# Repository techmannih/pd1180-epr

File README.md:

# NEMA34 48 V EPR controller — RP2040 redesign

[System block diagrams and operating sequence](https://github.com/techmannih/pd1180-epr/blob/main/docs/system-overview.md).

**Design revision 0.5.0-RP2040-DRAFT — implementation and commissioning handoff.** The source now uses RP2040, DRV8262DDVR with integrated power bridges, TPS26750 for the retained 48 V / 5 A EPR input, and an optional AS5600. The stocked-driver ECO follows merged PR #27 (`5035034`) and retains that 48 V architecture. Use the assembly and commissioning guides below to prepare the order and collect physical results after assembly.

Start with [the nine-sheet power/component review](https://github.com/techmannih/pd1180-epr/blob/main/docs/usb-pd-architecture.md), [current reference-board decisions](https://github.com/techmannih/pd1180-epr/blob/main/docs/reference-review.md), [the redesign and evidence](https://github.com/techmannih/pd1180-epr/blob/main/docs/rp2040-redesign.md), [reviewer checklist](https://github.com/techmannih/pd1180-epr/blob/main/docs/reviewer-checklist.md) and [firmware instructions](https://github.com/techmannih/pd1180-epr/blob/main/firmware/README.md). `index.circuit.tsx` is the current schematic/placement source. The DATA-only source, firmware and native route are synchronized. The paired native review archive contains fresh DRC/ERC reports: 8 retained USB hole-clearance errors, 488 cosmetic warnings, and zero other errors, unconnected items or schematic-parity/ERC findings. The older GUI screenshot is explicitly historical.

The new commissioning firmware is an ARM RP2040 image with verified ELF/BIN/UF2 format and matching source hashes. The default image remains diagnostics-only. Separate stationary-power and bounded motor-test profiles provide the post-assembly workflow: <=0.8 A RMS request, 10 rpm, 10 seconds, local START and automatic stop. Use [programming, readback and commissioning](https://github.com/techmannih/pd1180-epr/blob/main/docs/commissioning.md). Physical measurements are performed by the assembly/test team; the software results do not claim them.

The hosted preview opens `release/circuit.json`; its routed payload has been regenerated from the verified native board and checked against this DATA-only source. `index.circuit.tsx` remains editable; `bun run dev` opens that source. The PCB carries the matching 0.5 DRAFT revision marking.

| Function | This design |
| --- | --- |
| U16 MCU / U17 boot storage | RP2040 / W25Q32JV, 4 MiB QSPI flash, 12 MHz crystal; powered only from J10 DATA |
| U7 motor stage | DRV8262DDVR, top-cooled DDV package; PH/EN motion with U42 MCP4822 dual current references |
| Power | TPS26750 EPR sink, dedicated J1; independent DATA/logic-power J10 |
| PD monitoring | U38 INA237 measures raw PD_VBUS; ADS1115 retains protected VMOTOR. Fresh ADC conversion + TPS contract produce PD_READY; eFuse MOTOR_PG stays independent. |
| Terminals | J2 WAGO 2601-3104 motor; J3 WAGO 236-402 brake. No JST mating plugs; paired solder tails belong to each wire entry. |
| Encoder | AS5600 I²C, optional DNP U18 on bottom; C52/C53 on top |
| Protection | Independent eFuse, voltage window, thermal inhibit, hardware enable gates and external J3 braking resistor retained |
| Motor | STEPPERONLINE 34HS31-6004S1, 6 A/phase motor rating; initial bench-test requests <=0.8 A RMS |
| Mounting | Four motor-CAD-aligned holes; choose screws/spacers from measured rear thread/depth and physical fit |

For order preparation, use [fabrication and assembly instructions](https://github.com/techmannih/pd1180-epr/blob/main/docs/assembly.md), [the exact-part sourcing snapshot](https://github.com/techmannih/pd1180-epr/blob/main/docs/procurement.md) and [manufacturer acceptance checklist](https://github.com/techmannih/pd1180-epr/blob/main/docs/manufacturing-acceptance.md). They separate the supplied files/software from supplier allocation, installation and post-assembly measurements.

Source/firmware development checks:

```sh
bun install --frozen-lockfile
bunx tsci build index.circuit.tsx --routing-disabled --disable-parts-engine
bun run typecheck
bun run check:firmware-pins
bun run check:firmware
bun test scripts/rp2040-contract.test.mjs scripts/encoder-bypass-policy.test.mjs
bun run check:schematic-style
```

Run `bun run review` for all engineering and artifact checks; consult its generated report. The machine-readable release record separately retains manufacturer acceptance, sourcing and physical-test evidence.

The completed reviewer scope and remaining physical acceptance steps are in [the handoff](https://github.com/techmannih/pd1180-epr/blob/main/docs/completion-handoff.md). The [ordered-motor manufacturer STEP archive](https://github.com/techmannih/pd1180-epr/blob/main/engineering/mechanical/34HS31-6004S1-manufacturer.zip) establishes the rear hole axes; it does not approve replacement screws or engagement depth.

Previous-board context: [historical README](https://github.com/techmannih/pd1180-epr/blob/main/docs/legacy-stm32-tmc-readme.md). It is retained for review, not as evidence for the redesign.

**DATA-only MCU:** J10 supplies RP2040 even when J1 PD is connected. PD alone cannot run local controls. Board-side I²C and status signals are isolated through U39/U40; the brake retains independent motor-bus power. See [power domains](https://github.com/techmannih/pd1180-epr/blob/main/docs/usb-pd-architecture.md).

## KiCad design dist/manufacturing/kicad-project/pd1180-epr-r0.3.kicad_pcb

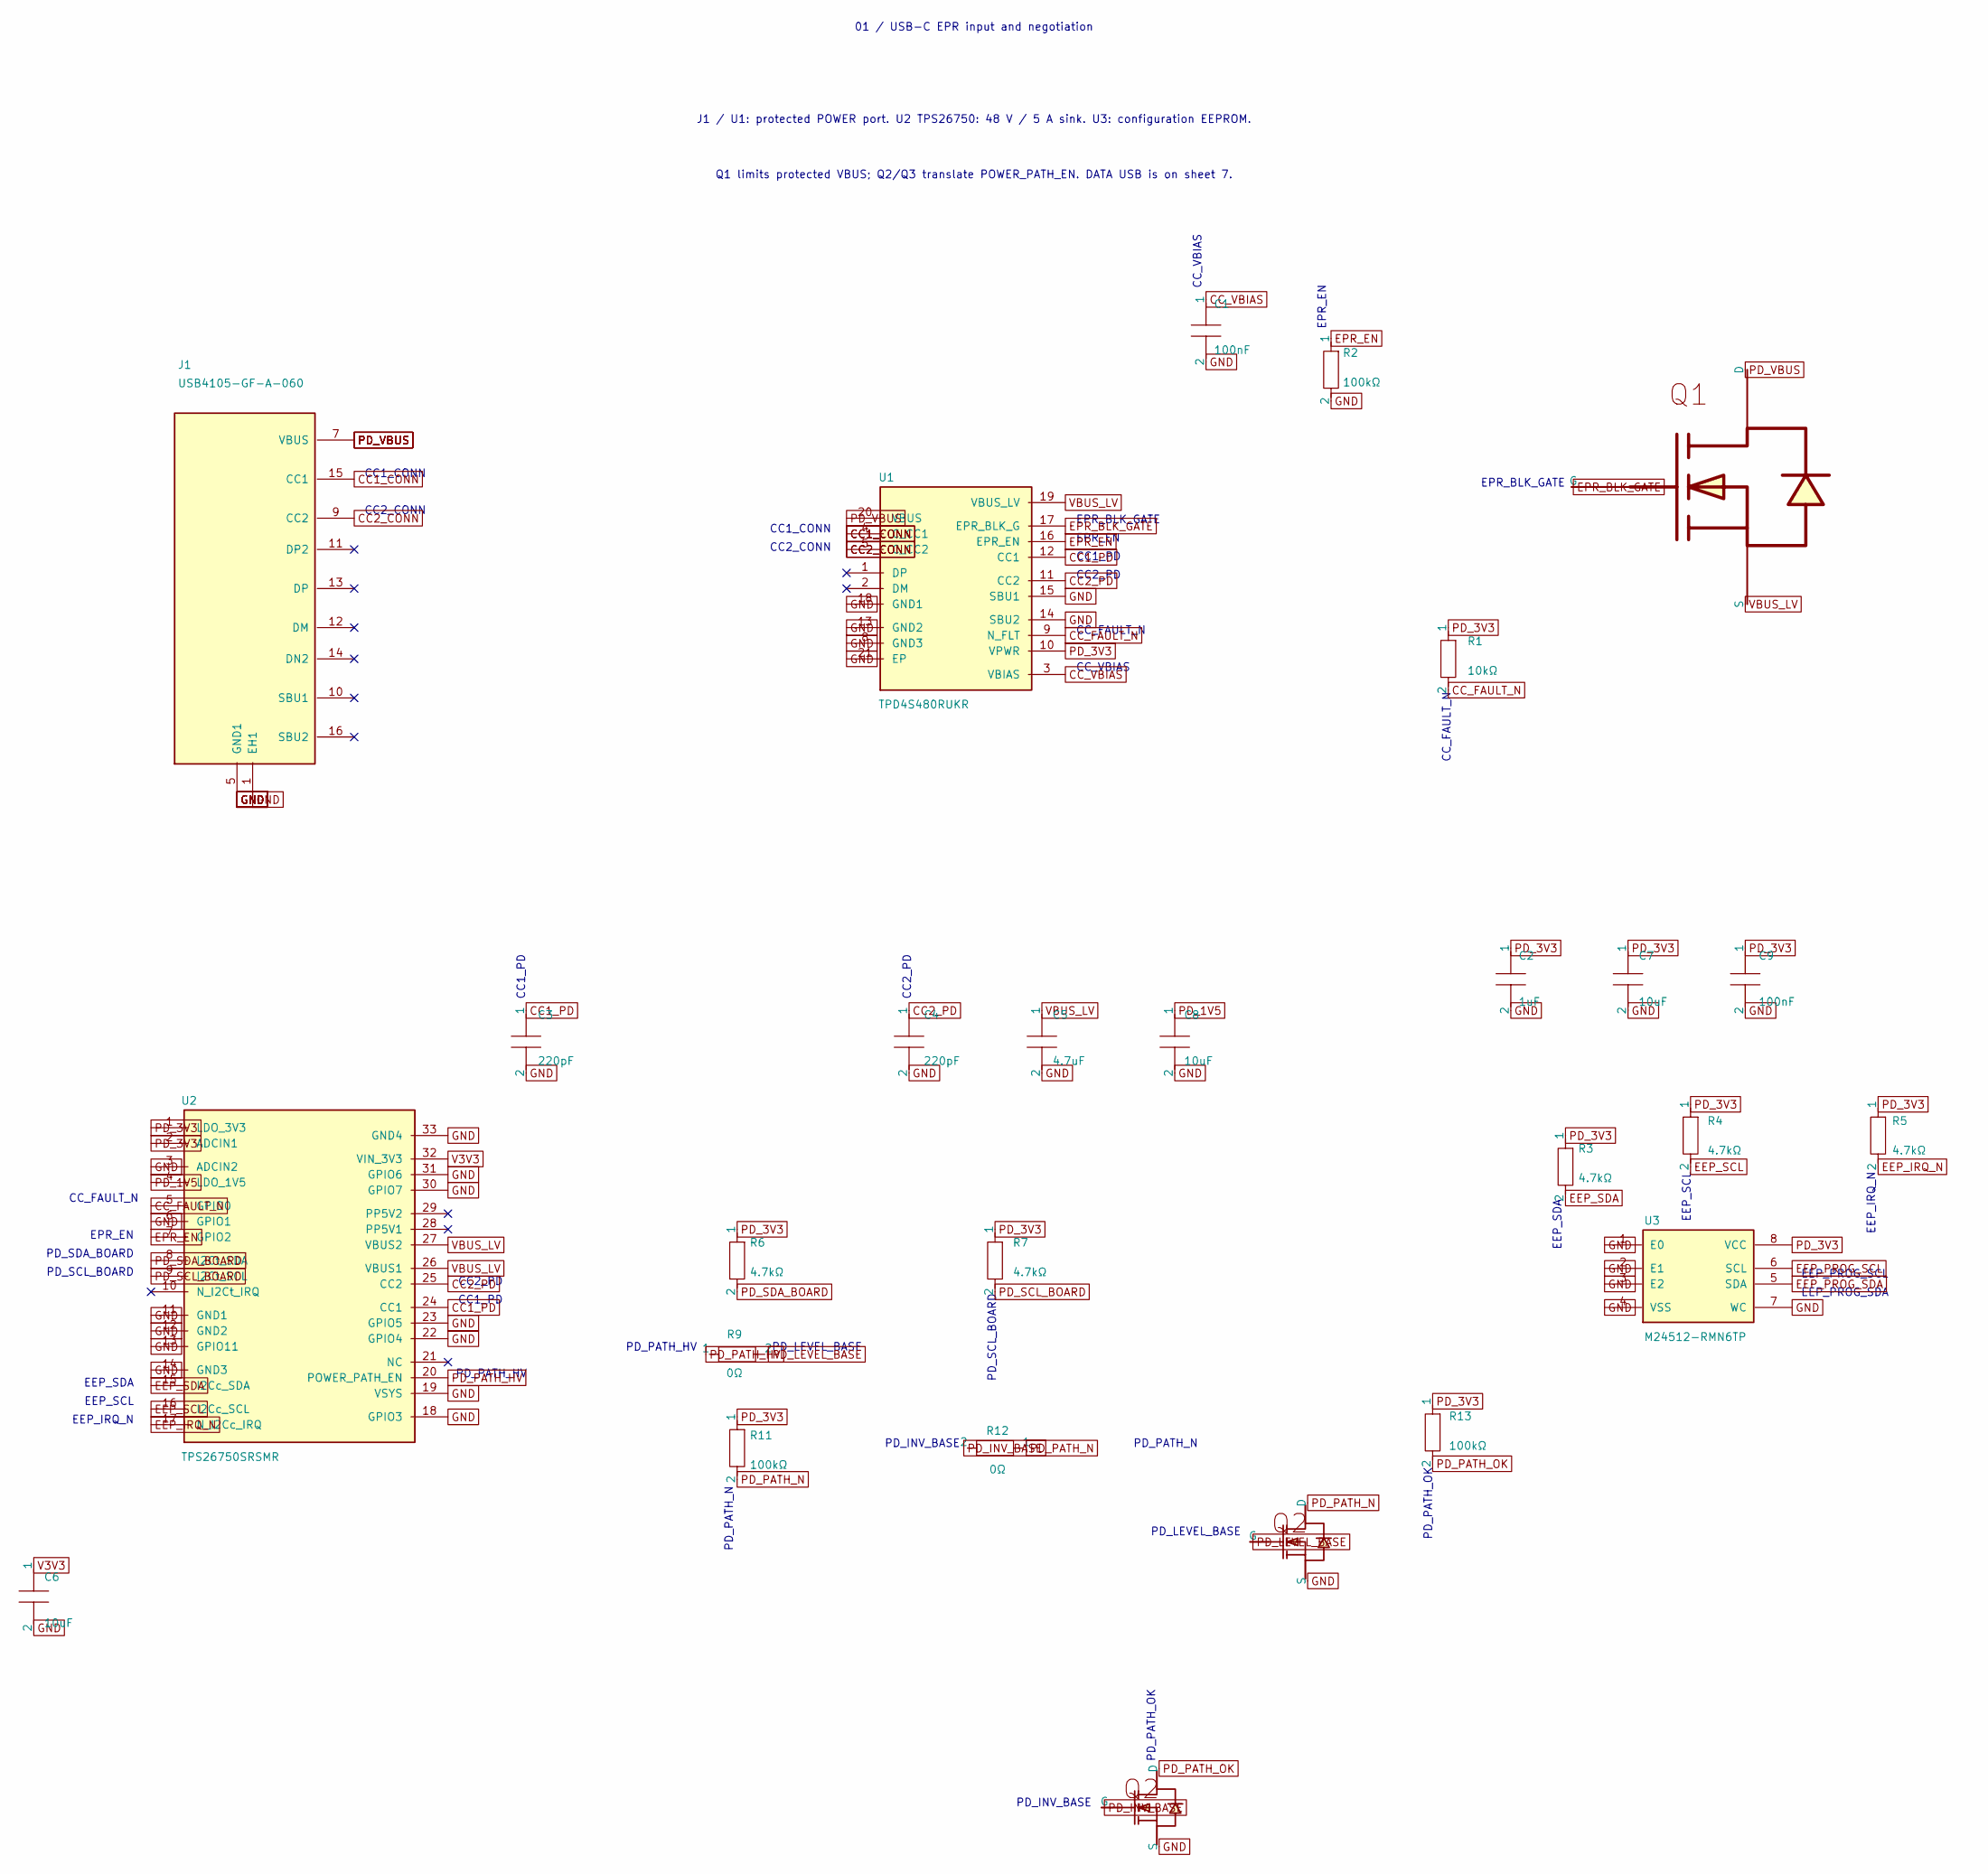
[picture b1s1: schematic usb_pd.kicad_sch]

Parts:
C1, C9: 100nF; capacitor_cap0603
C2: 1uF; capacitor_cap0603
C3, C4: 220pF; capacitor_cap0603
C5: 4.7uF; capacitor_cap1206
C6, C7, C8: 10uF; capacitor_cap0603
J1: USB4105-GF-A-060
Q1: BSS123LT1G
Q2, Q3: CSD17484F4
R1: 10kΩ; resistor_res0603
R2, R11, R13: 100kΩ; resistor_res0603
R3, R4, R5, R6, R7: 4.7kΩ; resistor_res0603
R9, R12: 0Ω; resistor_res0603
U1: TPD4S480RUKR
U2: TPS26750SRSMR
U3: M24512-RMN6TP

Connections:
CC1_CONN: J1.15 (CC1), U1.4 (C_CC1), U1.7 (C_CC1)
CC1_PD: C3.1, U1.12 (CC1), U2.24 (CC1)
CC2_CONN: J1.9 (CC2), U1.5 (C_CC2), U1.6 (C_CC2)
CC2_PD: C4.1, U1.11 (CC2), U2.25 (CC2)
CC_FAULT_N: R1.2, U1.9 (N_FLT), U2.5 (GPIO0)
CC_VBIAS: C1.1, U1.3 (VBIAS)
EEP_IRQ_N: R5.2, U2.17 (N_I2Cc_IRQ)
EEP_PROG_SCL: U3.6 (SCL); also elsewhere on the board
EEP_PROG_SDA: U3.5 (SDA); also elsewhere on the board
EEP_SCL: R4.2, U2.16 (I2Cc_SCL); also elsewhere on the board
EEP_SDA: R3.2, U2.15 (I2Cc_SDA); also elsewhere on the board
EPR_BLK_GATE: Q1.1 (G), U1.17 (EPR_BLK_G)
EPR_EN: R2.1, U1.16 (EPR_EN), U2.7 (GPIO2)
GND: C1.2, C2.2, C3.2, C4.2, C5.2, C6.2, C7.2, C8.2, C9.2, J1.1 (EH1), J1.2 (GND1), J1.3 (GND1), J1.4 (GND1), J1.5 (GND1), J1.6 (GND1), J1.19 (GND1), J1.20 (GND1), Q2.2 (S), Q3.2 (S), R2.2, U1.8 (GND3), U1.13 (GND2), U1.14 (SBU2), U1.15 (SBU1), U1.18 (GND1), U1.21 (EP), U2.3 (ADCIN2), U2.6 (GPIO1), U2.11 (GND1), U2.12 (GND2), U2.13 (GPIO11), U2.14 (GND3), U2.18 (GPIO3), U2.19 (VSYS), U2.22 (GPIO4), U2.23 (GPIO5), U2.30 (GPIO7), U2.31 (GPIO6), U2.33 (GND4), U3.1 (E0), U3.2 (E1), U3.3 (E2), U3.4 (VSS), U3.7 (WC); also elsewhere on the board
PD_1V5: C8.1, U2.4 (LDO_1V5)
PD_3V3: C2.1, C7.1, C9.1, R1.1, R3.1, R4.1, R5.1, R6.1, R7.1, R11.1, R13.1, U1.10 (VPWR), U2.1 (LDO_3V3), U2.2 (ADCIN1), U3.8 (VCC); also elsewhere on the board
PD_INV_BASE: Q3.1 (G), R12.2
PD_LEVEL_BASE: Q2.1 (G), R9.2
PD_PATH_HV: R9.1, U2.20 (POWER_PATH_EN)
PD_PATH_N: Q2.3 (D), R11.2, R12.1
PD_PATH_OK: Q3.3 (D), R13.2; also elsewhere on the board
PD_SCL_BOARD: R7.2, U2.9 (I2Ct_SCL); also elsewhere on the board
PD_SDA_BOARD: R6.2, U2.8 (I2Ct_SDA); also elsewhere on the board
PD_VBUS: J1.7 (VBUS), J1.8 (VBUS), J1.17 (VBUS), J1.18 (VBUS), Q1.3 (D), U1.20 (VBUS); also elsewhere on the board
V3V3: C6.1, U2.32 (VIN_3V3); also elsewhere on the board
VBUS_LV: C5.1, Q1.2 (S), U1.19 (VBUS_LV), U2.26 (VBUS1), U2.27 (VBUS2)

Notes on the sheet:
01 / USB-C EPR input and negotiation
J1 / U1: protected POWER port. U2 TPS26750: 48 V / 5 A sink. U3: configuration EEPROM.
Q1 limits protected VBUS; Q2/Q3 translate POWER_PATH_EN. DATA USB is on sheet 7.
CC2_CONN
CC1_CONN
CC_VBIAS
CC_FAULT_N
CC2_PD
CC1_PD
EPR_EN
PD_PATH_N
EPR_BLK_GATE
PD_SDA_BOARD
PD_SCL_BOARD
EEP_SDA
EEP_SCL
EEP_IRQ_N
PD_PATH_HV
EEP_PROG_SDA
EEP_PROG_SCL
PD_LEVEL_BASE
PD_INV_BASE
PD_PATH_OK

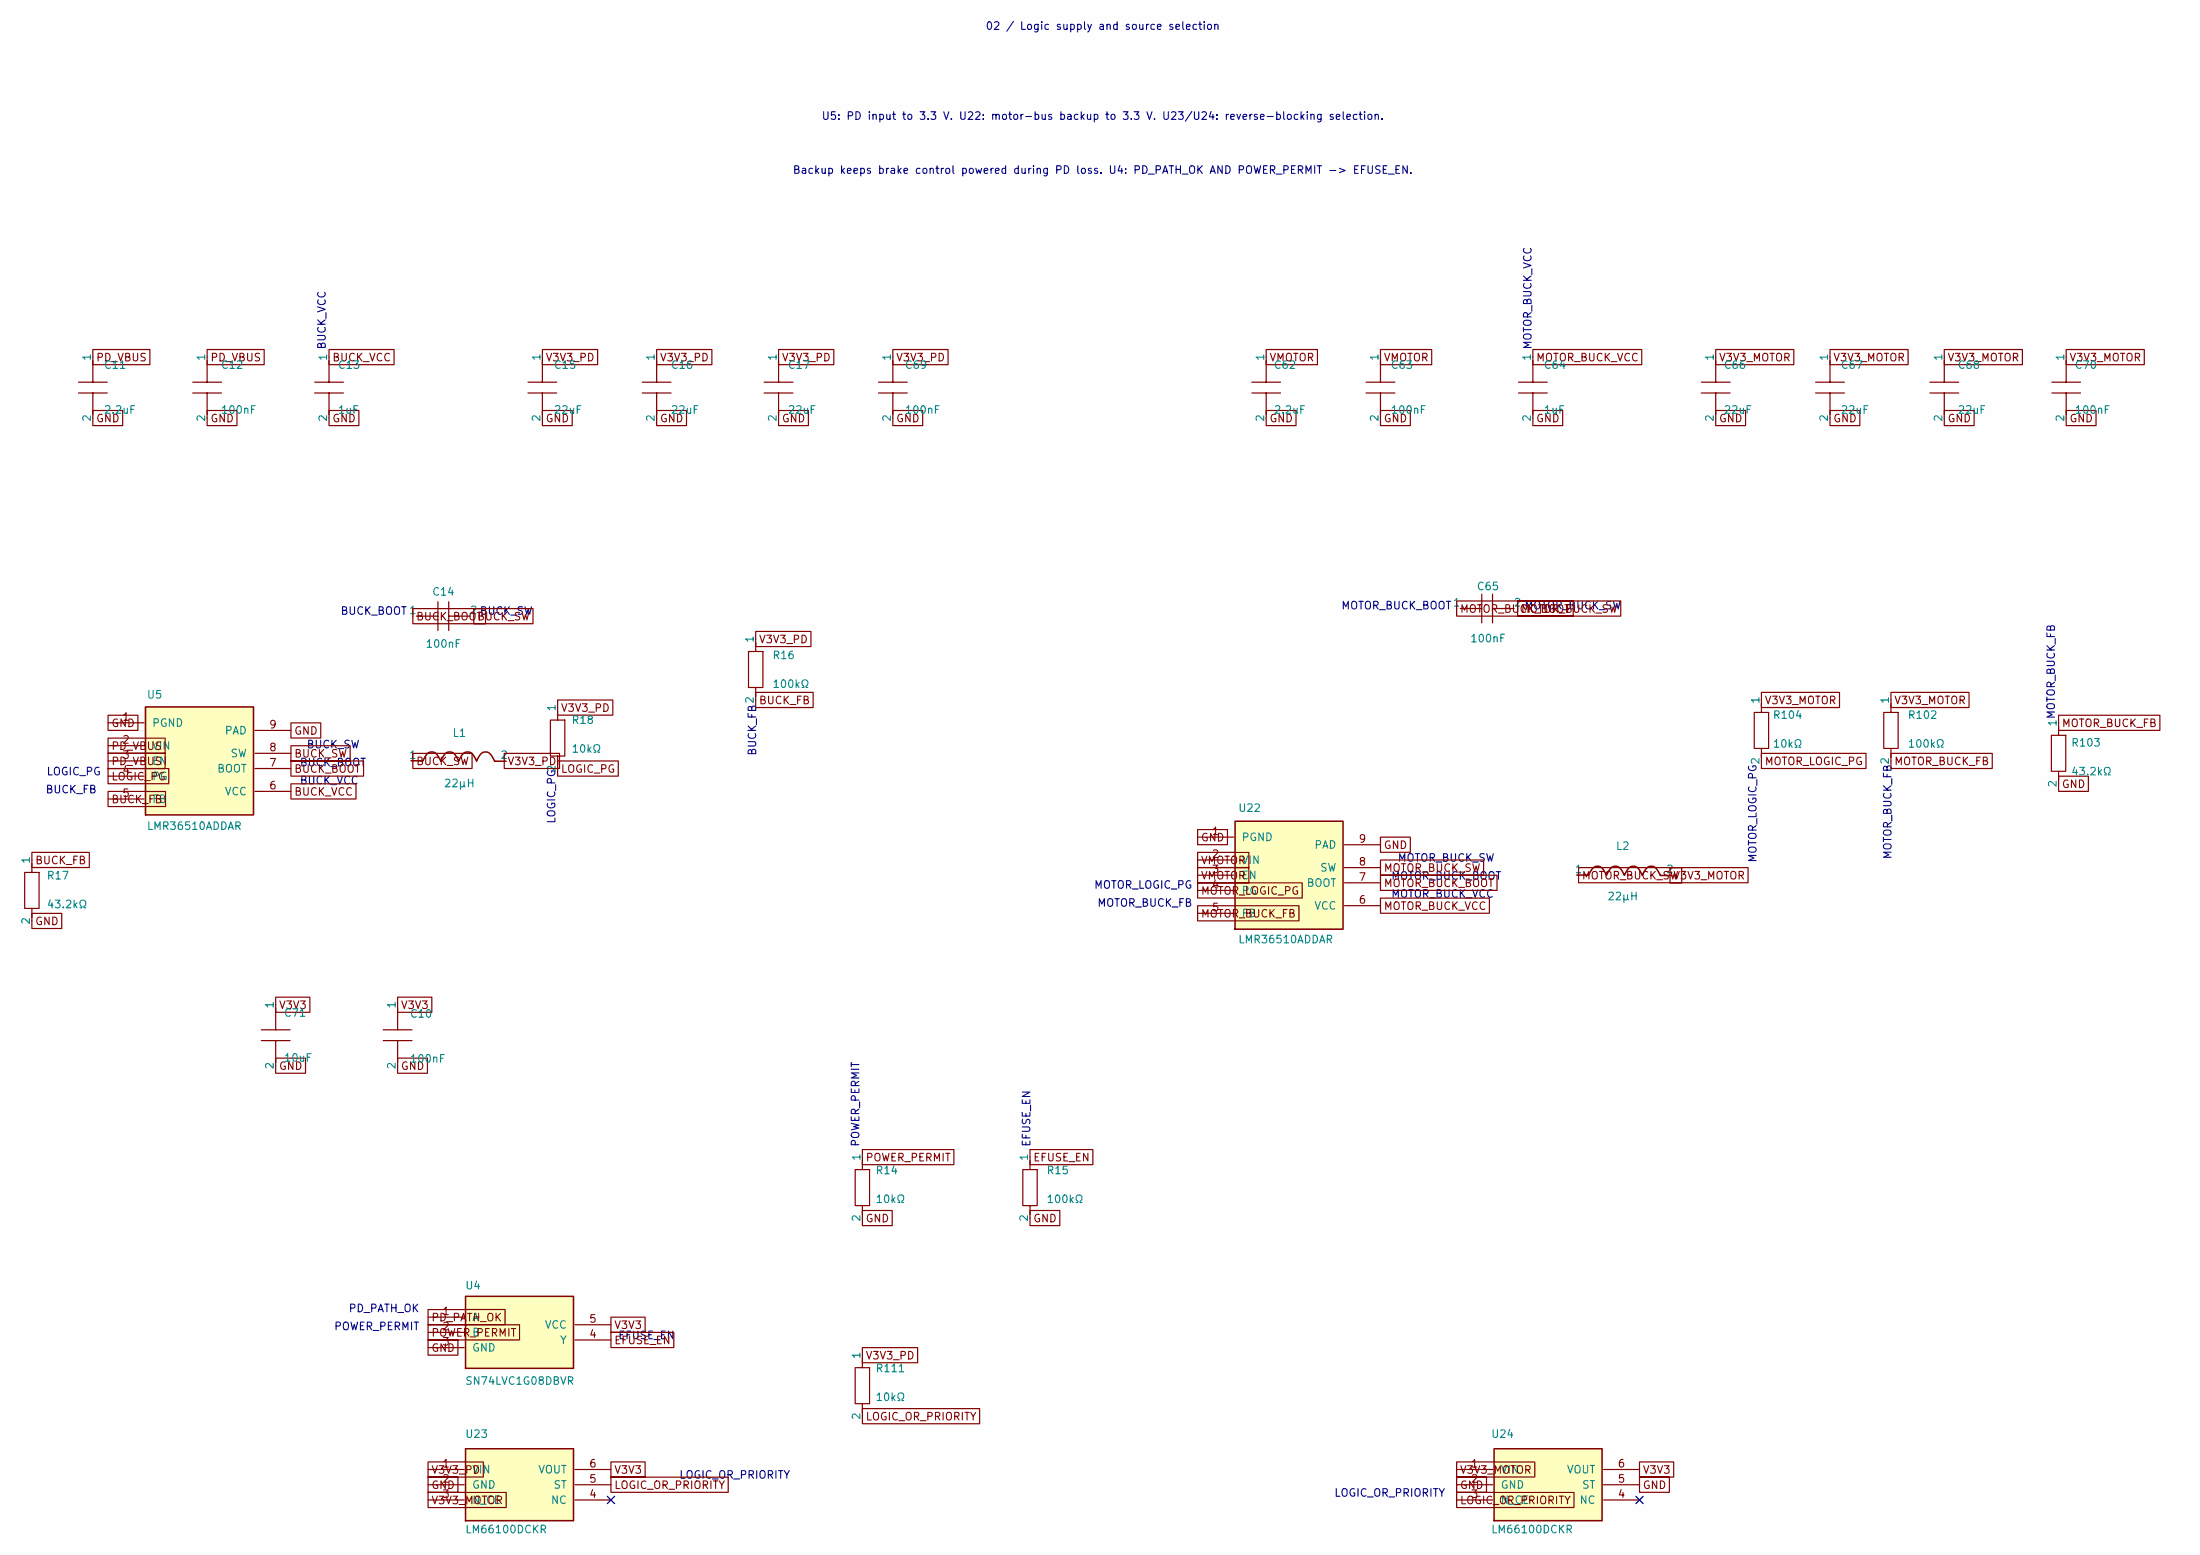
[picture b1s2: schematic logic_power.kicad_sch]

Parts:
C10, C12, C14, C63, C65, C69, C70: 100nF; capacitor_cap0603
C11, C62: 2.2uF; capacitor_cap1206
C13, C64: 1uF; capacitor_cap0603
C15, C16, C17, C66, C67, C68: 22uF; capacitor_cap0805
C71: 10uF; capacitor_cap0603
L1, L2: 22µH; SWPA6045S220MT
R14, R18, R104, R111: 10kΩ; resistor_res0603
R15, R16, R102: 100kΩ; resistor_res0603
R17, R103: 43.2kΩ; resistor_res0603
U4: SN74LVC1G08DBVR
U5, U22: LMR36510ADDAR
U23, U24: LM66100DCKR

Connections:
BUCK_BOOT: C14.1, U5.7 (BOOT)
BUCK_FB: R16.2, R17.1, U5.5 (FB)
BUCK_SW: C14.2, L1.1, U5.8 (SW)
BUCK_VCC: C13.1, U5.6 (VCC)
EFUSE_EN: R15.1, U4.4 (Y); also elsewhere on the board
GND: C10.2, C11.2, C12.2, C13.2, C15.2, C16.2, C17.2, C62.2, C63.2, C64.2, C66.2, C67.2, C68.2, C69.2, C70.2, C71.2, R14.2, R15.2, R17.2, R103.2, U4.3 (GND), U5.1 (PGND), U5.9 (PAD), U22.1 (PGND), U22.9 (PAD), U23.2 (GND), U24.2 (GND), U24.5 (ST); also elsewhere on the board
LOGIC_OR_PRIORITY: R111.2, U23.5 (ST), U24.3 (N_CE)
LOGIC_PG: R18.2, U5.4 (PG); also elsewhere on the board
MOTOR_BUCK_BOOT: C65.1, U22.7 (BOOT)
MOTOR_BUCK_FB: R102.2, R103.1, U22.5 (FB)
MOTOR_BUCK_SW: C65.2, L2.1, U22.8 (SW)
MOTOR_BUCK_VCC: C64.1, U22.6 (VCC)
MOTOR_LOGIC_PG: R104.2, U22.4 (PG)
PD_PATH_OK: U4.1 (A); also elsewhere on the board
PD_VBUS: C11.1, C12.1, U5.2 (VIN), U5.3 (EN); also elsewhere on the board
POWER_PERMIT: R14.1, U4.2 (B); also elsewhere on the board
V3V3: C10.1, C71.1, U4.5 (VCC), U23.6 (VOUT), U24.6 (VOUT); also elsewhere on the board
V3V3_MOTOR: C66.1, C67.1, C68.1, C70.1, L2.2, R102.1, R104.1, U23.3 (N_CE), U24.1 (VIN)
V3V3_PD: C15.1, C16.1, C17.1, C69.1, L1.2, R16.1, R18.1, R111.1, U23.1 (VIN)
VMOTOR: C62.1, C63.1, U22.2 (VIN), U22.3 (EN); also elsewhere on the board

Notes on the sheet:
02 / Logic supply and source selection
U5: PD input to 3.3 V. U22: motor-bus backup to 3.3 V. U23/U24: reverse-blocking selection.
Backup keeps brake control powered during PD loss. U4: PD_PATH_OK AND POWER_PERMIT -> EFUSE_EN.
PD_PATH_OK
POWER_PERMIT
EFUSE_EN
LOGIC_PG
BUCK_FB
BUCK_SW
MOTOR_BUCK_FB
MOTOR_BUCK_SW
LOGIC_OR_PRIORITY
BUCK_VCC
BUCK_BOOT
MOTOR_LOGIC_PG
MOTOR_BUCK_VCC
MOTOR_BUCK_BOOT

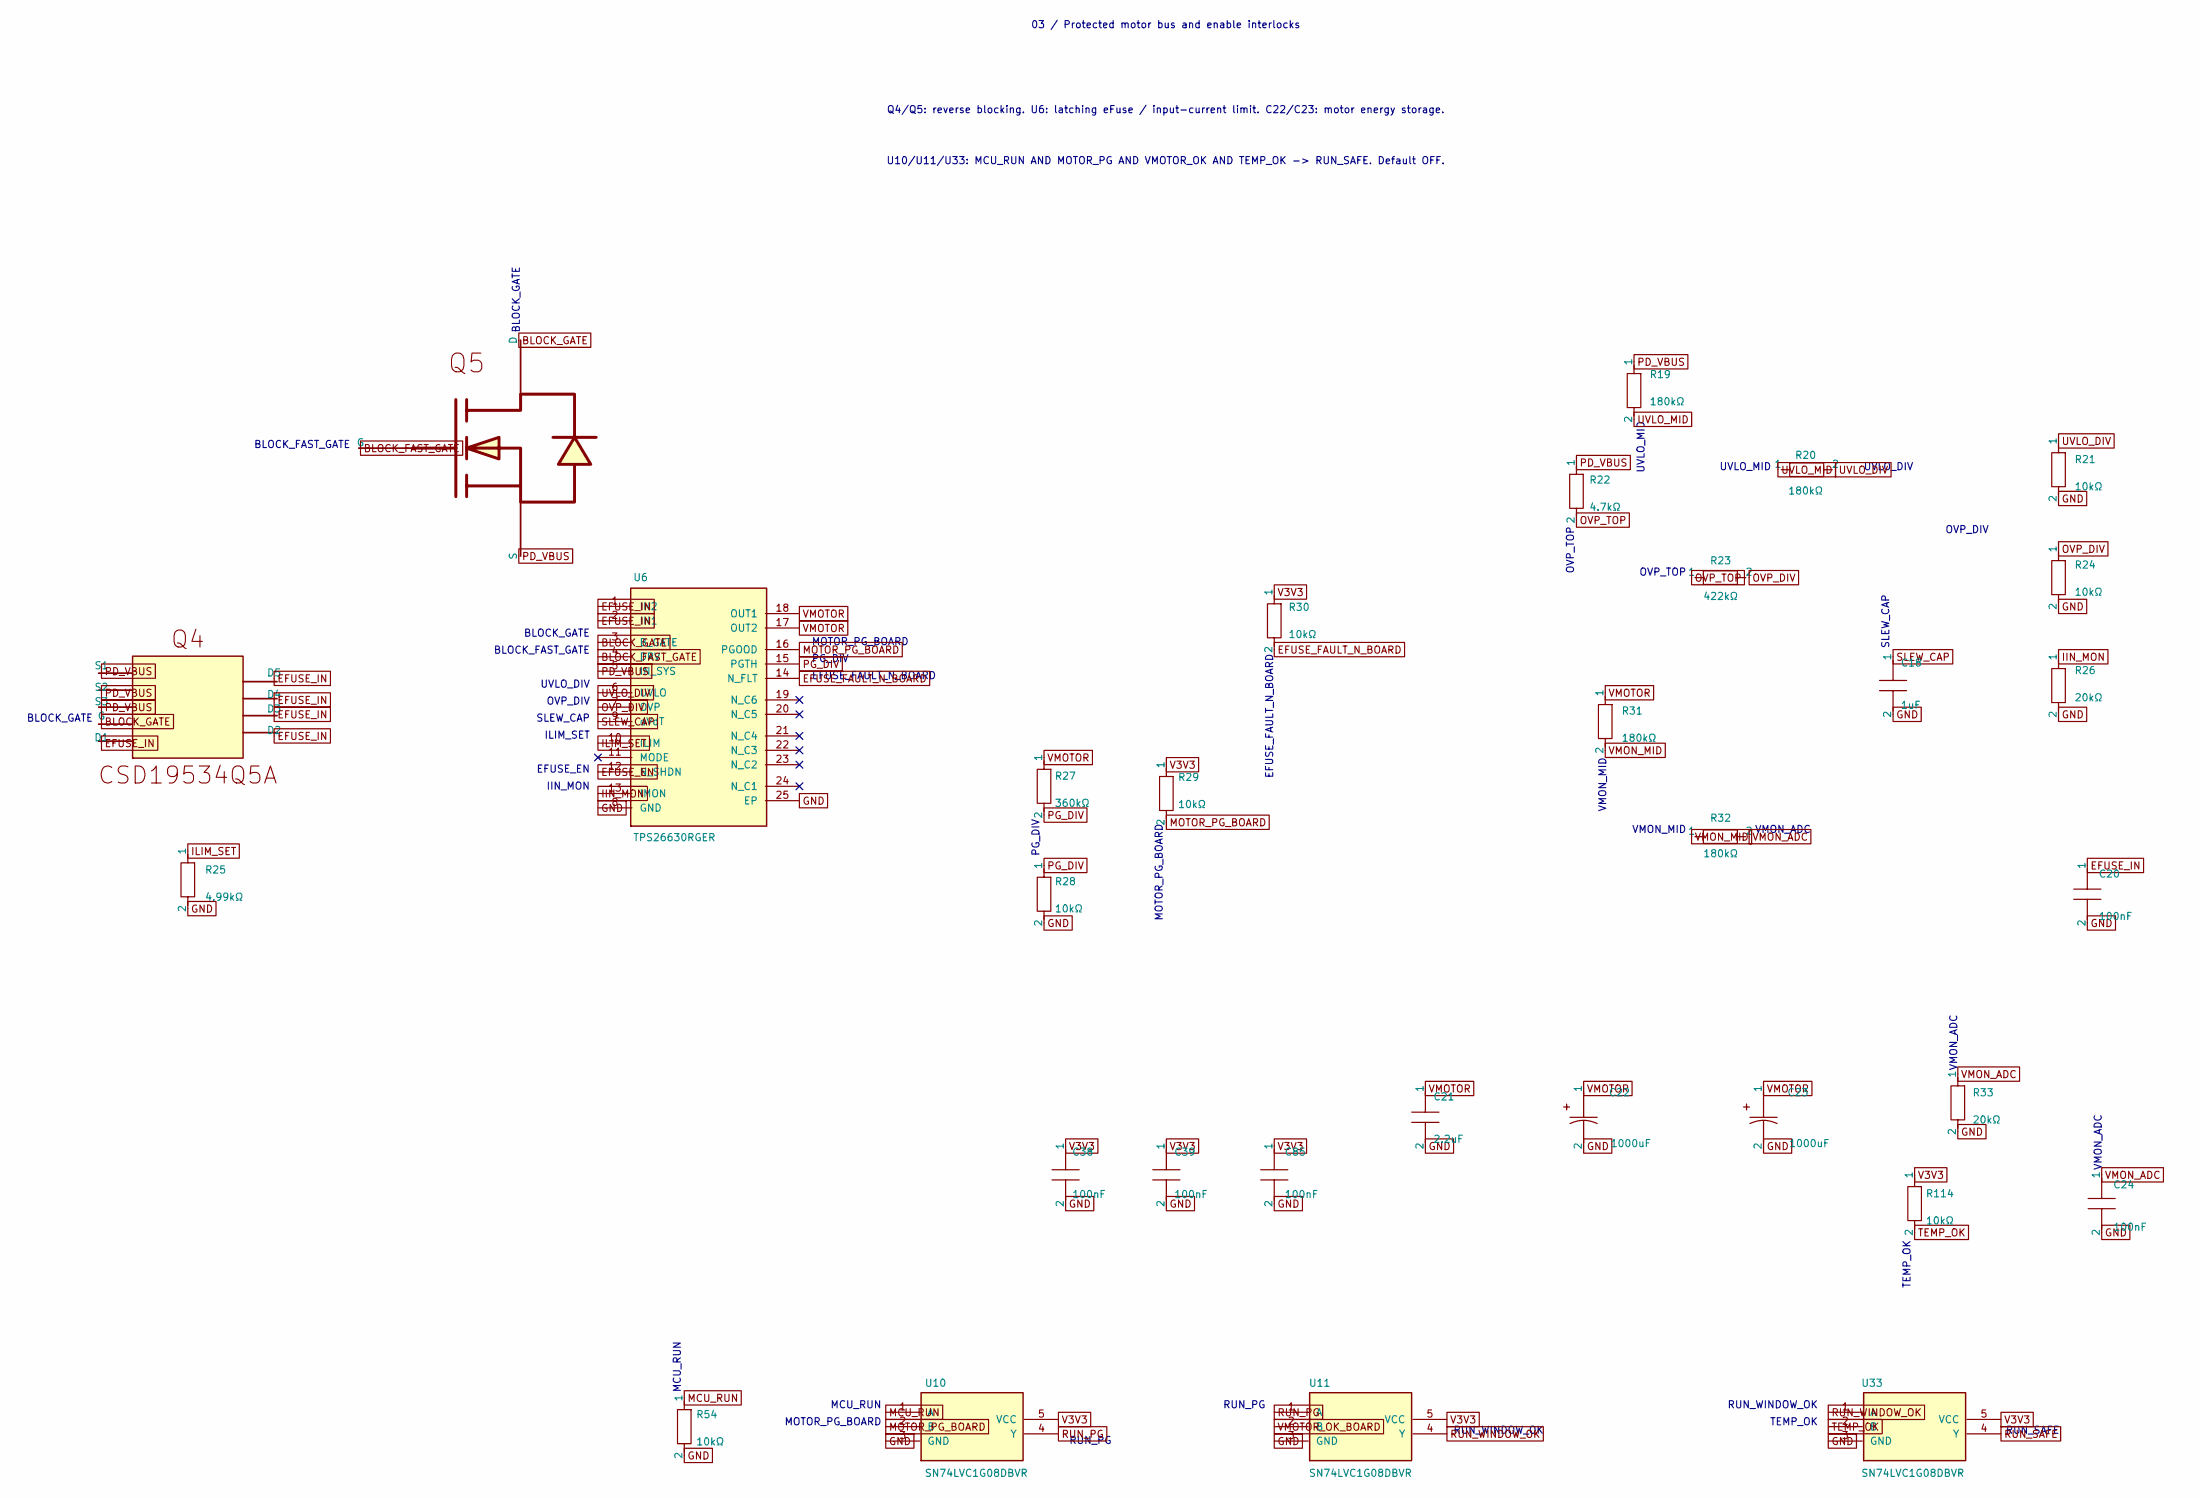
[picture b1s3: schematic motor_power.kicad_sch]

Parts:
C18: 1uF; capacitor_cap0603
C20, C24, C38, C39, C85: 100nF; capacitor_cap0603
C21: 2.2uF; capacitor_cap1206
C22, C23: 1000uF; EEUFS1J102
Q4: CSD19534Q5A
Q5: BSS123LT1G
R19, R20, R31, R32: 180kΩ; resistor_res0603
R21, R24, R28, R29, R30, R54, R114: 10kΩ; resistor_res0603
R22: 4.7kΩ; resistor_res0603
R23: 422kΩ; resistor_res0603
R25: 4.99kΩ; resistor_res0603
R26, R33: 20kΩ; resistor_res0603
R27: 360kΩ; resistor_res0603
U6: TPS26630RGER
U10, U11, U33: SN74LVC1G08DBVR

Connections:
BLOCK_FAST_GATE: Q5.1 (G), U6.4 (DRV)
BLOCK_GATE: Q4.4 (G), Q5.3 (D), U6.3 (B_GATE)
EFUSE_EN: U6.12 (N_SHDN); also elsewhere on the board
EFUSE_FAULT_N_BOARD: R30.2, U6.14 (N_FLT); also elsewhere on the board
EFUSE_IN: C20.1, Q4.5 (D1), Q4.6 (D2), Q4.7 (D3), Q4.8 (D4), Q4.9 (D5), U6.1 (IN2), U6.2 (IN1)
GND: C18.2, C20.2, C21.2, C22.2, C23.2, C24.2, C38.2, C39.2, C85.2, R21.2, R24.2, R25.2, R26.2, R28.2, R33.2, R54.2, U6.8 (GND), U6.25 (EP), U10.3 (GND), U11.3 (GND), U33.3 (GND); also elsewhere on the board
IIN_MON: R26.1, U6.13 (IMON); also elsewhere on the board
ILIM_SET: R25.1, U6.10 (ILIM)
MCU_RUN: R54.1, U10.1 (A); also elsewhere on the board
MOTOR_PG_BOARD: R29.2, U6.16 (PGOOD), U10.2 (B); also elsewhere on the board
OVP_DIV: R23.2, R24.1, U6.7 (OVP)
OVP_TOP: R22.2, R23.1
PD_VBUS: Q4.1 (S1), Q4.2 (S2), Q4.3 (S3), Q5.2 (S), R19.1, R22.1, U6.5 (IN_SYS); also elsewhere on the board
PG_DIV: R27.2, R28.1, U6.15 (PGTH)
RUN_PG: U10.4 (Y), U11.1 (A)
RUN_SAFE: U33.4 (Y); also elsewhere on the board
RUN_WINDOW_OK: U11.4 (Y), U33.1 (A)
SLEW_CAP: C18.1, U6.9 (dVdT)
TEMP_OK: R114.2, U33.2 (B); also elsewhere on the board
UVLO_DIV: R20.2, R21.1, U6.6 (UVLO)
UVLO_MID: R19.2, R20.1
V3V3: C38.1, C39.1, C85.1, R29.1, R30.1, R114.1, U10.5 (VCC), U11.5 (VCC), U33.5 (VCC); also elsewhere on the board
VMON_ADC: C24.1, R32.2, R33.1; also elsewhere on the board
VMON_MID: R31.2, R32.1
VMOTOR: C21.1, C22.1, C23.1, R27.1, R31.1, U6.17 (OUT2), U6.18 (OUT1); also elsewhere on the board
VMOTOR_OK_BOARD: U11.2 (B); also elsewhere on the board

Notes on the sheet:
03 / Protected motor bus and enable interlocks
Q4/Q5: reverse blocking. U6: latching eFuse / input-current limit. C22/C23: motor energy storage.
U10/U11/U33: MCU_RUN AND MOTOR_PG AND VMOTOR_OK AND TEMP_OK -> RUN_SAFE. Default OFF.
BLOCK_GATE
UVLO_DIV
OVP_DIV
PG_DIV
MOTOR_PG_BOARD
VMON_ADC
BLOCK_FAST_GATE
SLEW_CAP
ILIM_SET
EFUSE_EN
IIN_MON
EFUSE_FAULT_N_BOARD
UVLO_MID
OVP_TOP
VMON_MID
MCU_RUN
RUN_PG
RUN_WINDOW_OK
TEMP_OK
RUN_SAFE

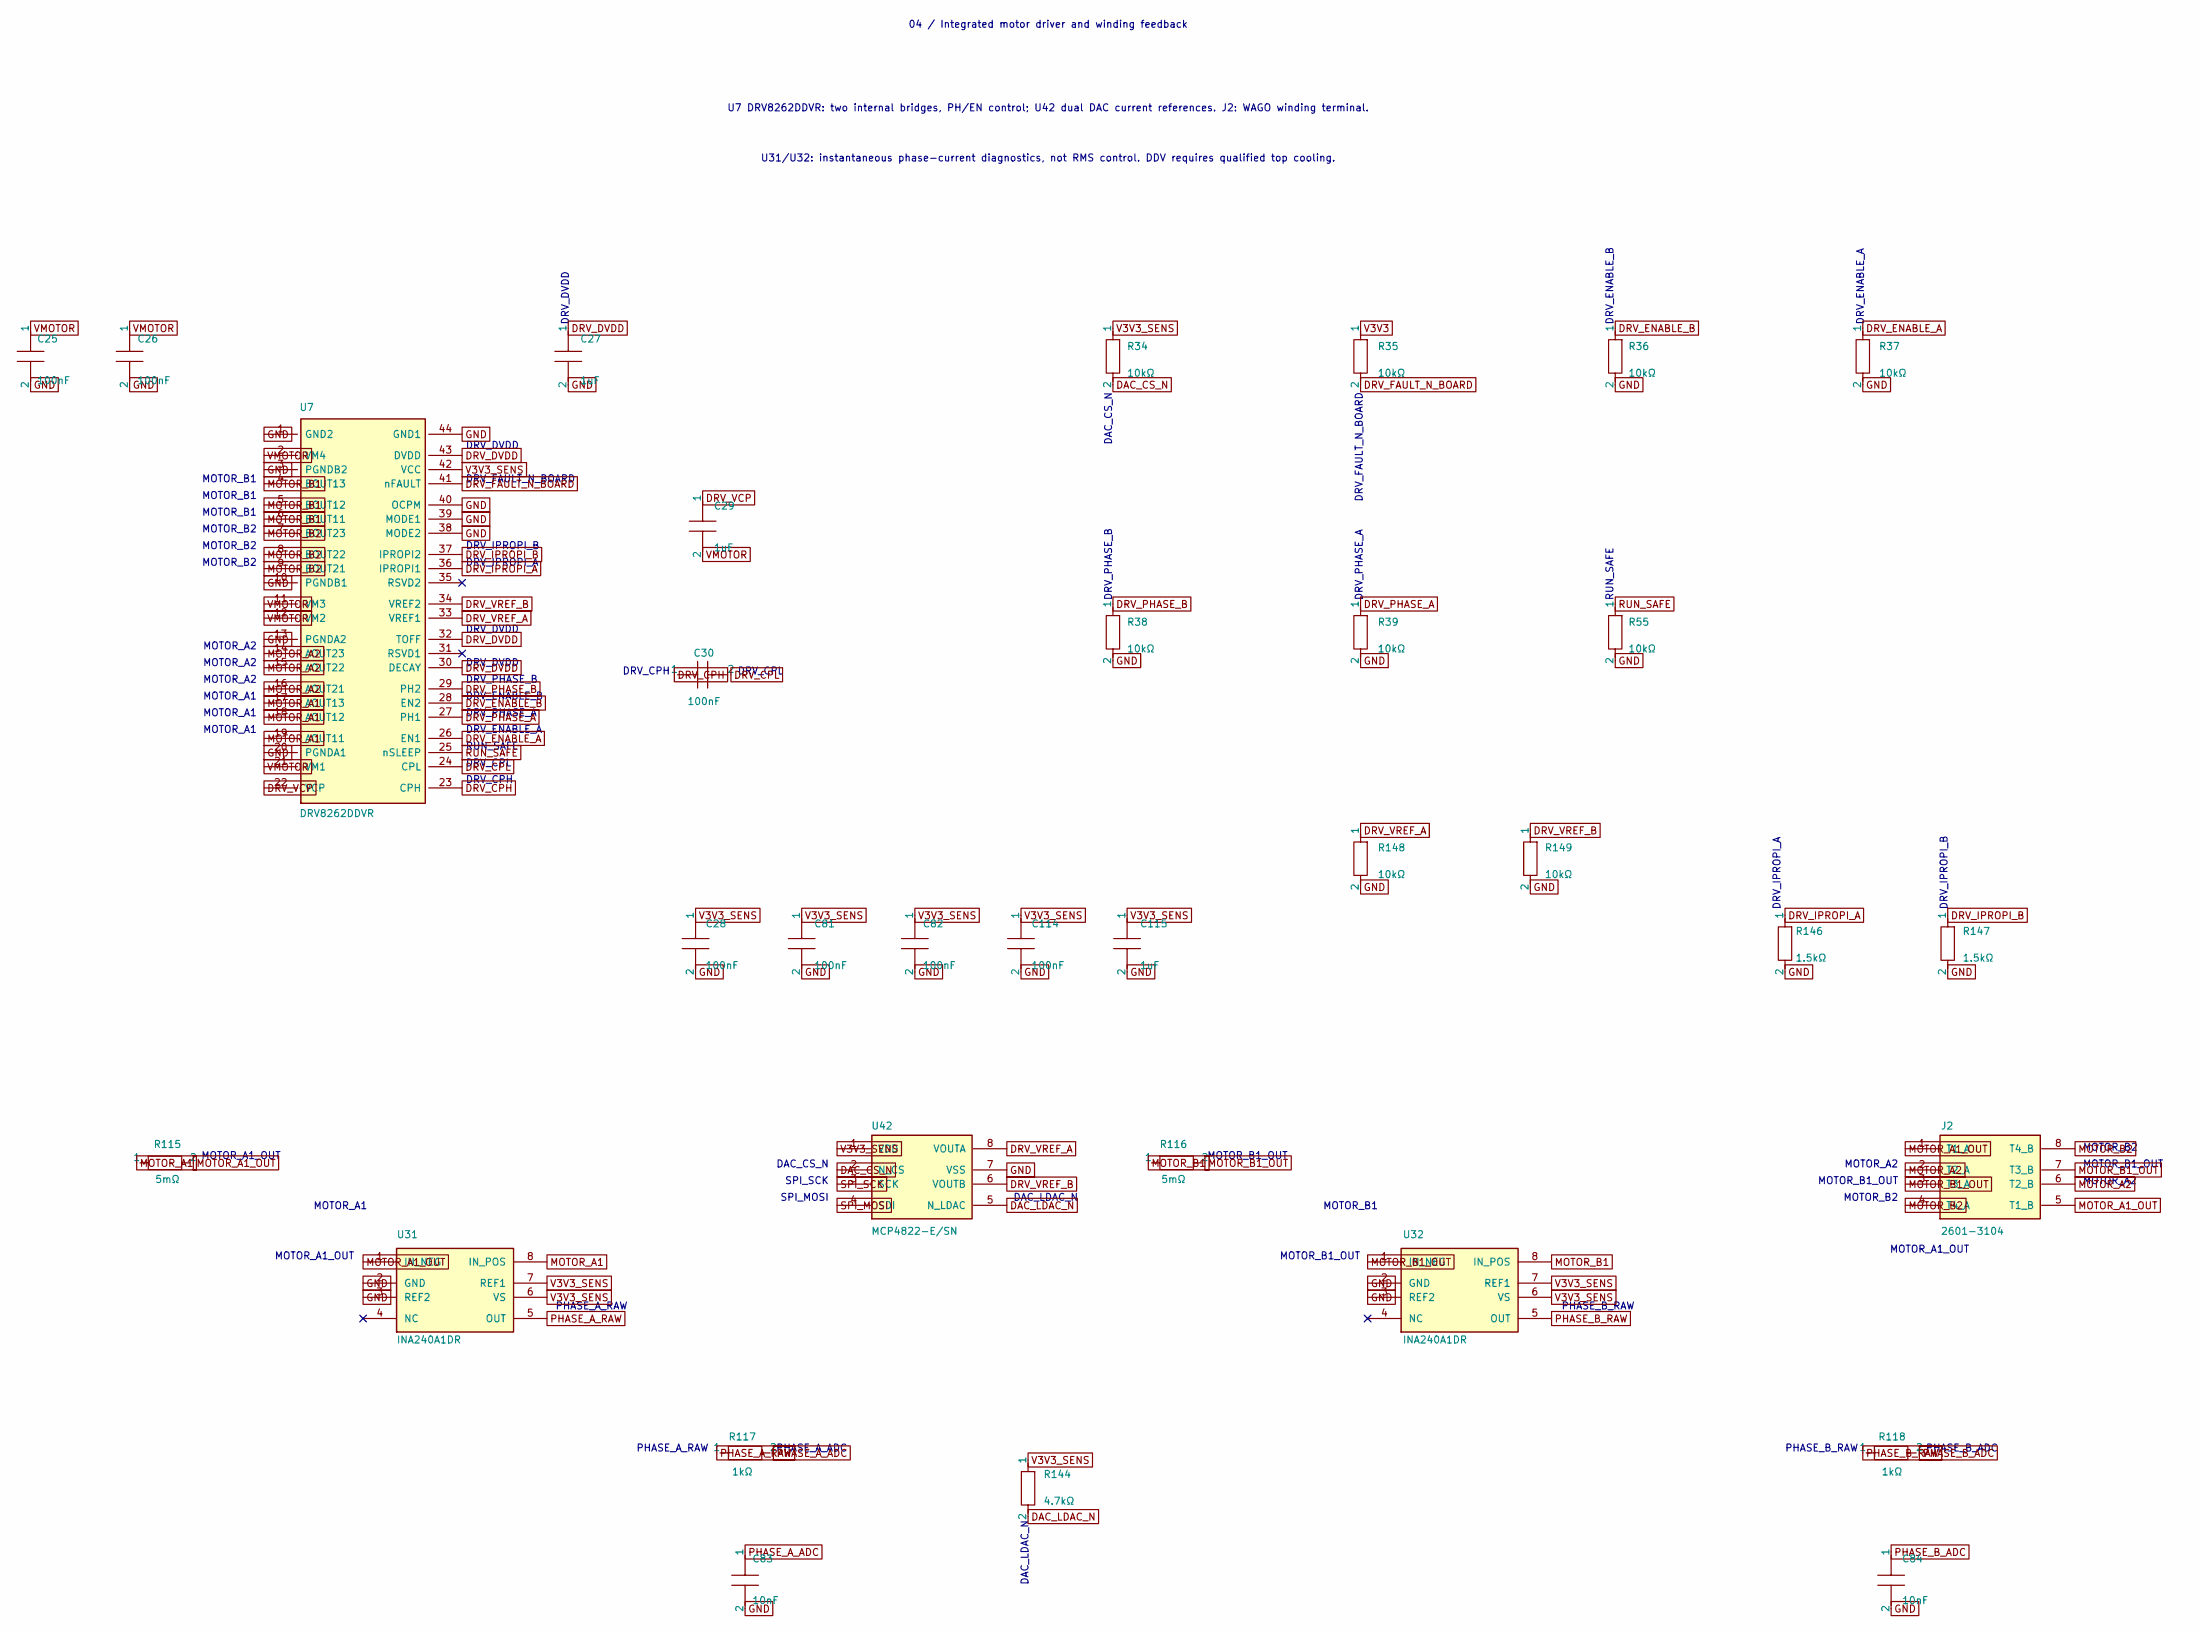
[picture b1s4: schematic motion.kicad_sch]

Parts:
C25, C26, C30: 100nF; capacitor_cap0805
C27, C29, C115: 1uF; capacitor_cap0603
C28, C81, C82, C114: 100nF; capacitor_cap0603
C83, C84: 10nF; capacitor_cap0603
J2: 2601-3104
R34, R35, R36, R37, R38, R39, R55, R148, R149: 10kΩ; resistor_res0603
R115, R116: 5mΩ; FRM121WFR005TM
R117, R118: 1kΩ; resistor_res0603
R144: 4.7kΩ; resistor_res0603
R146, R147: 1.5kΩ; resistor_res0603
U7: DRV8262DDVR
U31, U32: INA240A1DR
U42: MCP4822-E/SN; MCP4822-E_SN

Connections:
DAC_CS_N: R34.2, U42.2 (N_CS); also elsewhere on the board
DAC_LDAC_N: R144.2, U42.5 (N_LDAC); also elsewhere on the board
DRV_CPH: C30.1, U7.23 (CPH)
DRV_CPL: C30.2, U7.24 (CPL)
DRV_DVDD: C27.1, U7.30 (DECAY), U7.32 (TOFF), U7.43 (DVDD)
DRV_ENABLE_A: R37.1, U7.26 (EN1); also elsewhere on the board
DRV_ENABLE_B: R36.1, U7.28 (EN2); also elsewhere on the board
DRV_FAULT_N_BOARD: R35.2, U7.41 (nFAULT); also elsewhere on the board
DRV_IPROPI_A: R146.1, U7.36 (IPROPI1)
DRV_IPROPI_B: R147.1, U7.37 (IPROPI2)
DRV_PHASE_A: R39.1, U7.27 (PH1); also elsewhere on the board
DRV_PHASE_B: R38.1, U7.29 (PH2); also elsewhere on the board
DRV_VCP: C29.1, U7.22 (VCP)
DRV_VREF_A: R148.1, U7.33 (VREF1), U42.8 (VOUTA)
DRV_VREF_B: R149.1, U7.34 (VREF2), U42.6 (VOUTB)
GND: C25.2, C26.2, C27.2, C28.2, C81.2, C82.2, C83.2, C84.2, C114.2, C115.2, R36.2, R37.2, R38.2, R39.2, R55.2, R146.2, R147.2, R148.2, R149.2, U7.1 (GND2), U7.3 (PGNDB2), U7.10 (PGNDB1), U7.13 (PGNDA2), U7.20 (PGNDA1), U7.38 (MODE2), U7.39 (MODE1), U7.40 (OCPM), U7.44 (GND1), U31.2 (GND), U31.3 (REF2), U32.2 (GND), U32.3 (REF2), U42.7 (VSS); also elsewhere on the board
MOTOR_A1: R115.1, U7.17 (AOUT13), U7.18 (AOUT12), U7.19 (AOUT11), U31.8 (IN_POS)
MOTOR_A1_OUT: J2.1 (T1_A), J2.5 (T1_B), R115.2, U31.1 (IN_NEG)
MOTOR_A2: J2.2 (T2_A), J2.6 (T2_B), U7.14 (AOUT23), U7.15 (AOUT22), U7.16 (AOUT21)
MOTOR_B1: R116.1, U7.4 (BOUT13), U7.5 (BOUT12), U7.6 (BOUT11), U32.8 (IN_POS)
MOTOR_B1_OUT: J2.3 (T3_A), J2.7 (T3_B), R116.2, U32.1 (IN_NEG)
MOTOR_B2: J2.4 (T4_A), J2.8 (T4_B), U7.7 (BOUT23), U7.8 (BOUT22), U7.9 (BOUT21)
PHASE_A_ADC: C83.1, R117.2; also elsewhere on the board
PHASE_A_RAW: R117.1, U31.5 (OUT)
PHASE_B_ADC: C84.1, R118.2; also elsewhere on the board
PHASE_B_RAW: R118.1, U32.5 (OUT)
RUN_SAFE: R55.1, U7.25 (nSLEEP); also elsewhere on the board
SPI_MOSI: U42.4 (SDI); also elsewhere on the board
SPI_SCK: U42.3 (SCK); also elsewhere on the board
V3V3: R35.1; also elsewhere on the board
V3V3_SENS: C28.1, C81.1, C82.1, C114.1, C115.1, R34.1, R144.1, U7.42 (VCC), U31.6 (VS), U31.7 (REF1), U32.6 (VS), U32.7 (REF1), U42.1 (VDD); also elsewhere on the board
VMOTOR: C25.1, C26.1, C29.2, U7.2 (VM4), U7.11 (VM3), U7.12 (VM2), U7.21 (VM1); also elsewhere on the board

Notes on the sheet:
04 / Integrated motor driver and winding feedback
U7 DRV8262DDVR: two internal bridges, PH/EN control; U42 dual DAC current references. J2: WAGO winding terminal.
U31/U32: instantaneous phase-current diagnostics, not RMS control. DDV requires qualified top cooling.
DAC_CS_N
SPI_SCK
SPI_MOSI
DAC_LDAC_N
DRV_IPROPI_A
DRV_IPROPI_B
MOTOR_B1
MOTOR_B2
MOTOR_A2
MOTOR_A1
DRV_DVDD
MOTOR_A1_OUT
MOTOR_B1_OUT
DRV_CPH
DRV_CPL
RUN_SAFE
DRV_ENABLE_A
DRV_PHASE_A
DRV_ENABLE_B
DRV_PHASE_B
DRV_FAULT_N_BOARD
PHASE_A_RAW
PHASE_A_ADC
PHASE_B_RAW
PHASE_B_ADC
